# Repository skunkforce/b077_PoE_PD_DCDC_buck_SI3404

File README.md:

# edgy_board number b077
This design is part of the [edgy board project](https://github.com/skunkforce/edgy_boards). 

# getting started
This repository uses submodules. After cloning use the command 

```$ git submodule update --init --recursive```

to pull the submodules before opening the project with kicad. 

# Tests
Tests can be found in [TESTS.md](TESTS.md)

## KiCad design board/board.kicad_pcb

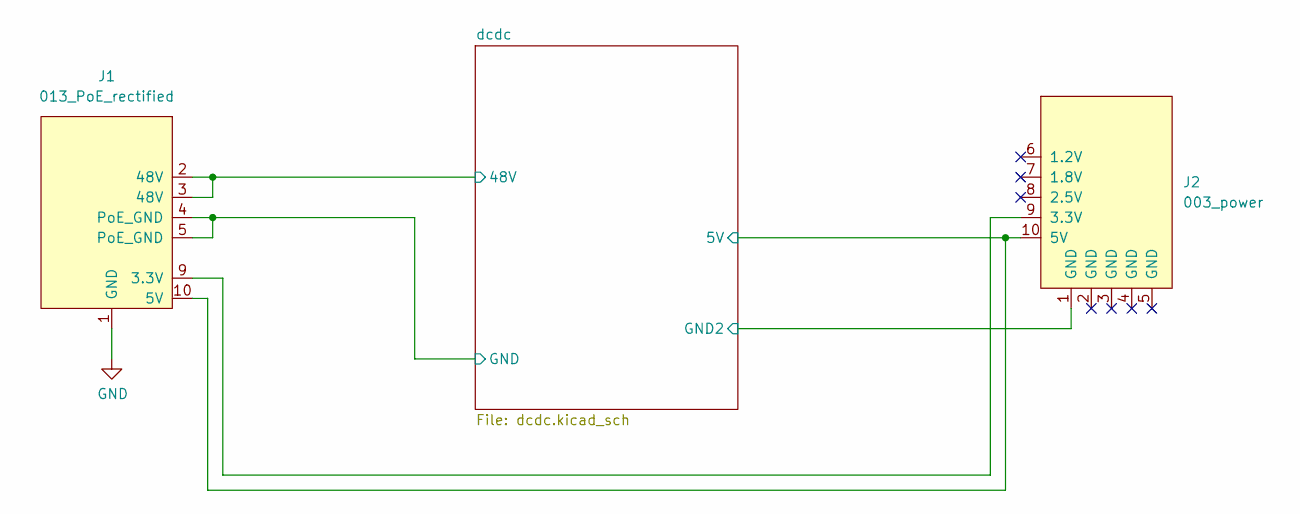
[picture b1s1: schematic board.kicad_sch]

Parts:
J1: 013_PoE_rectified; on_edge_2x05_device
J2: 003_power; on_edge_2x05_host

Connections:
/dcdc/5V: J1.10 (5V), J2.10 (5V); also elsewhere on the board
/dcdc/48V: J1.2 (48V), J1.3 (48V); also elsewhere on the board
/dcdc/GND: J1.4 (PoE_GND), J1.5 (PoE_GND); also elsewhere on the board
/dcdc/GND2: J2.1 (GND); also elsewhere on the board
GND: J1.1 (GND)
unnamed: J1.9 (3.3V), J2.9 (3.3V)

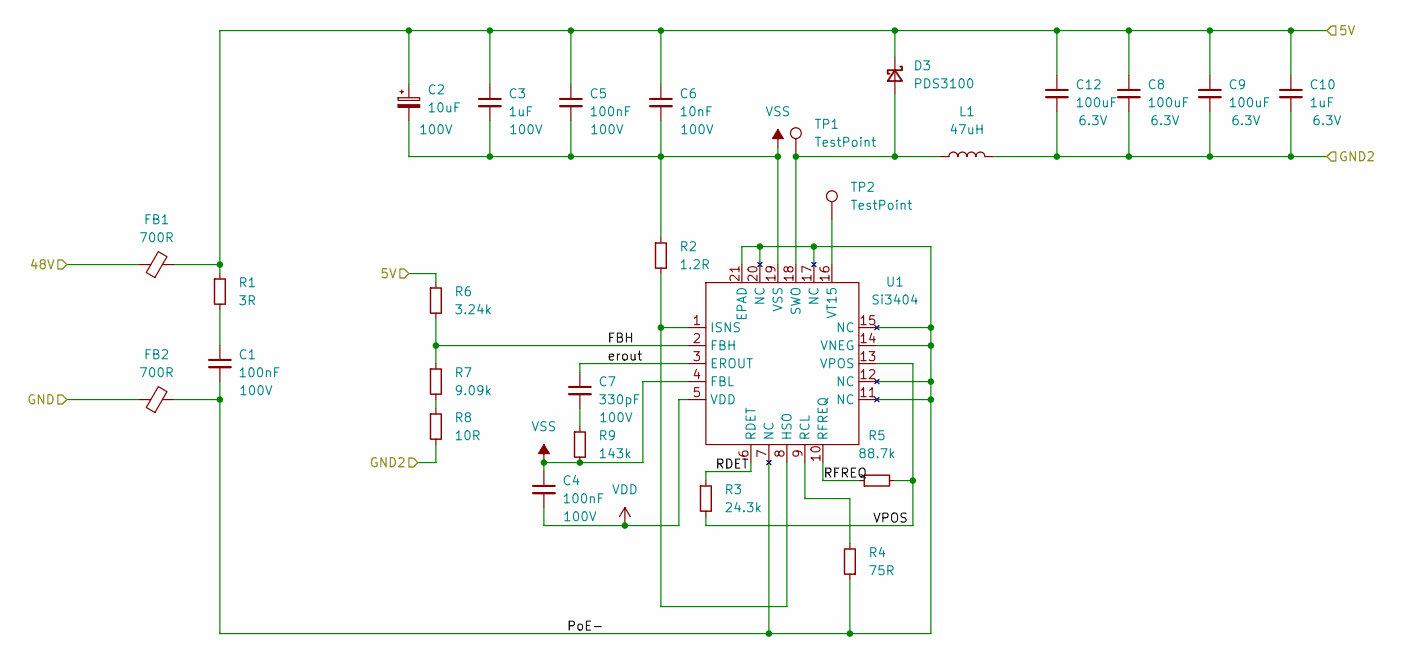
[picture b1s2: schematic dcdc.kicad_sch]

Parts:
C1, C5: 100nF; C_1210_3225Metric; Voltage 100V
C2: 10uF; CP_Elec_10x10; Voltage 100V
C3: 1uF; C_1210_3225Metric; Voltage 100V
C4: 100nF; C_0603_1608Metric; Voltage 100V
C6: 10nF; C_1210_3225Metric; Voltage 100V
C7: 330pF; C_0603_1608Metric; Voltage 100V
C8, C9, C12: 100uF; C_0805_2012Metric; Voltage 6.3V
C10: 1uF; C_0603_1608Metric; Voltage 6.3V
D3: PDS3100; D_PowerDI-5; Voltage 100V; MPN PDS3100-13
FB1, FB2: 700R; L_0805_2012Metric; MPN 742792040
L1: 47uH; L_10.4x10.4_H4.8; MPN MSS1038-473ML
R1: 3R; R_0603_1608Metric
R2: 1.2R; R_0805_2012Metric
R3: 24.3k; R_0603_1608Metric
R4: 75R; R_0603_1608Metric
R5: 88.7k; R_0603_1608Metric
R6: 3.24k; R_0603_1608Metric
R7: 9.09k; R_0603_1608Metric
R8: 10R; R_0603_1608Metric
R9: 143k; R_0603_1608Metric
TP1, TP2: TestPoint
U1: Si3404; QFN-20-1EP_4x4mm_P0.5mm_EP2.5x2.5mm_ThermalVias; MPN SI3404-A-GM

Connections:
/dcdc/5V: C2.1, C3.1, C5.1, C6.1, C8.1, C9.1, C10.1, C12.1, D3.1 (K), FB1.2, R1.1, R6.1; also elsewhere on the board
/dcdc/48V: FB1.1; also elsewhere on the board
/dcdc/FBH: R6.2, R7.1, U1.2 (FBH)
/dcdc/GND: FB2.1; also elsewhere on the board
/dcdc/GND2: C8.2, C9.2, C10.2, C12.2, L1.2, R8.2; also elsewhere on the board
/dcdc/PoE-: C1.2, FB2.2, R4.1, U1.7 (NC), U1.11 (NC), U1.12 (NC), U1.14 (VNEG), U1.15 (NC), U1.17 (NC), U1.20 (NC), U1.21 (EPAD)
/dcdc/RDET: R3.1, U1.6 (RDET)
/dcdc/RFREQ: R5.1, U1.10 (RFREQ)
/dcdc/VPOS: R3.2, R5.2, U1.13 (VPOS)
/dcdc/erout: C7.1, U1.3 (EROUT)
unnamed: C1.1, R1.2
unnamed: C7.2, R9.1
unnamed: D3.2 (A), L1.1, TP1.1, U1.18 (SWO)
unnamed: R2.2, U1.1 (ISNS), U1.8 (HSO)
unnamed: R4.2, U1.9 (RCL)
unnamed: R7.2, R8.1
unnamed: TP2.1, U1.16 (VT15)
VDD: C4.2, U1.5 (VDD)
VSS: C2.2, C3.2, C4.1, C5.2, C6.2, R2.1, R9.2, U1.4 (FBL), U1.19 (VSS)

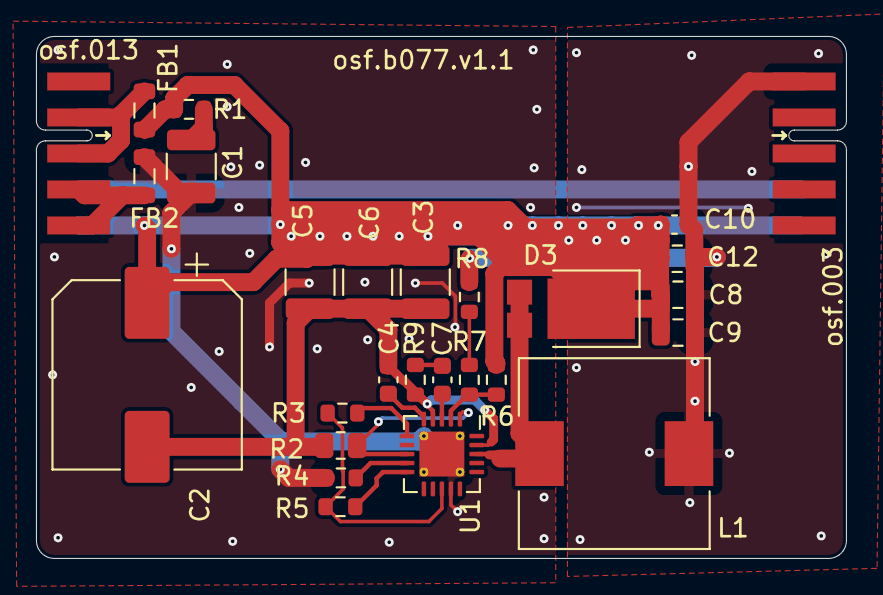
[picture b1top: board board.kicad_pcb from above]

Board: 2 copper layers, 45.0 x 29.0 mm, 27 parts (0 on the bottom side), 19 nets.

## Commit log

2023-04-02 initial
